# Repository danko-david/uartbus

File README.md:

# UARTBus and infrastructure

## Goal of the project
The project goal is to connect microcontrollers together on wire at minimal
cost (wiring, external peripheral components) and build a decentralized
sensor-actuator network where the node's can interact with each other and 
the microcontroller's software can be upgraded from the bus. This bus should be
connectable to a computer system (Desktop/Server PC, Raspberry PI, etc) to
achieve complex controlling by interacting with the sensors, actuators with
higher level softwares.

## Solution

The way to satisfy these requirement is to design and implement:
  
- new bus system for microcontrollers based on UART peripheral,
- lightweight RPC library for microcontrollers,
- bus gateway for computers,
- so called "host program" that implements common functionalities and manages
	application upload into the microcontroller. 
- a utility to connect softwares to the bus (through bus gateway)
- a higher level representation of bus devices (implemented in java)

## Feature list:

** Features related to bus: **

- microcontrollers connected together using built in UART peripheral and only
	one (pair when no ground) wire
- The bus forms a node based (device with address) network, but can be used
	to construct message based network like CAN.
- This is a multi master bus: any node can send message to any other node and
	vica-versa.
- Supports broadcast messages and that way device groups (negative device 
	addresses).
- Handles transmission collisions, retransmit and has a simple anti flood
	protection
- Interrupt based packet receive (send happens in blocking mode for now)
- Packet transmission based on transmission/idle time slots
- The core (ub) library is designed to be device agnostic and can even connect
	to multiple bus at same time when there's more UART peripheral available.
- The project contains a small footprint RPC library with function namespace
	capability used to order functions into namespaces like in OOP languages.
- variable length addressing

** Features related to the infrastructure: **

- The project contains a so called 'uart bootloader' (that's a wrong name, it
	should be host application or something else) that implements basic
	functionalities and code upload capability. Of course applications written
	directly for the microcontroller won't work, but i've created an
	`app_wrapper` used to compile applications can be uploaded to a node.
	TODO compiler, source, etc
- The project contains a bus gateway source written for ATMega2560, used to
	connect PC to an UARTBus.
- Java: At the PC side there's a server application (written in java) that makes
	the bus available through a JSON RPC server, this makes possible multiple PC
	application to connect the bus simultaneously even for different languages.
- Rust: the same CLI as one small executable without JVM, for embedded computers
	(Raspberry PI, routers), see [source/rust/uartbus](./source/rust/uartbus/README.md).
- Java: CLI application: `ping` to ping nodes, `console` to send command to
	devices, `packetloss` to measure packet loss ratio between bus gateway
	and node, `collisionPacketloss` to measure packet loss and duplication
	when send a broadcast packets that results race to access the bus.
	`upload` upload application code to a device with has uartbus bootloader on
	the board.

## Example usage

TODO: There's an easier way to try it out by yourself, using only arduino
and generic FETs (or BJTs with no opening delay in switching mode)

## Documentation

See: [Documentation index](./doc/index.md)   
All level and detail are implemented as small portion and bound so loosely
together to anyone can reuse the smaller piece of building blocks for custom
project.  

Eg: you can use OSI-{1,2} levels and skip the upper ones and
create a message based bus like as the CAN bus works. Or reverse: use CAN on the
lowest level and use the infrastructure.

## Short implementation explanation

### OSI-1: Physical layer

The bus data line consist of one wire pulled up to the bus Vcc voltage.
This line can be pulled down by any node used to transfer data.

The microcontroller's UART port is connected to the bus using bus driver: 

(During the development: Vcc = 12V; Rbus = 500Ω; Rtx = 0Ω; 
Rin & Ronline = 10 KΩ; 120m twisted pair for GND and Bus wire; 115,2 kbps)
(Note: this BS170 tolerates ±20V of Ugs voltage so can be connected directly to
the bus wire, but this might be risky when dealing with high transient voltage.
Solution: Connect TVS diode between `Bus` and `GND` wire. See documentation)

This is a simple level driver which makes the byte sent on the TX port appears
in the `Bus` line and data appears on the `Bus` wire translated to the RX port
with the proper logic level. This also means what we send on the TX we receive
on the RX. This used for transmission error and collision detection.

- Channel 1, Red: Bus wire signal 2 V/Div 
- Channel 2, Yellow: RX wire signal 1 V/Div

### OSI-2: Datalink layer

In this context, packet is interpreted as a sequence of byte in a time frame.
The time frame starts at the first sent byte and ends after the time of 2
(default value, but configurable) byte time transmission idle period.

A demonstration of UARTBus packages with collision handling (and retransmission)
using two nodes plus one bus gateway.
(This is an early development oscillogramm, timing not properly optimized)

- Channel 1, Red: Bus wire signal 2 V/Div 
- Channel 2, Yellow: RX wire signal of the first device 1 V/Div

1) Bus gateway sends a broadcast ping packet
2) Collision occurred, both node cancels the transmission and step back for a
	random time (longer wait time to the next transmission start)
	(Ethernets style collision handling)
3) First node "wins the arbitration" and sends the response pong packet
4) Second node also retransmit the pong packet that collided previously
5) No packet to send. Back to idle state.

### OSI-3: Network layer

Every node receives every packets on bus. This makes possible to create
broadcast addresses (0 is a general broadcast address) and device groups by
using negative addresses for this purpose.

Instead of using fixed int{8,16,32,64}_t for addressing, i've created a so
called variable length addressing:

- If we choose int8_t, every packet has only two byte of overhead at the
	addressing, but only 128 group 1 broadcast and 127 device address available.
- If we choose int32_t, every packet has 8 byte overhead, but addresses can go
	at group to 2_147_483_648, one broadcast and 2_147_483_647 device address.

To balance between this extreme cases i've created an encoder/decoder that
enables short address bytes when addresses are low (between -64 and +63) and 
increase address length when assign higher addresses.

|   | 7. bit | 6. bit | 5. bit | 4. bit | 3. bit | 2. bit | 1. bit | 0. bit |  
| --- |:---:|:---:|:---:|:---:|:---:|:---:|:---:|:---:|  
| First byte | E | S | A5 | A4 | A3 | A2 | A1 | A0 |  
| Nth byte | E | A6 | A5 | A4 | A3 | A2 | A1 | A0 |  

Byte scheme:

- E: Extend: Address continued on the next byte. The in last address byte this
	bit is 0. 
- S: Signum: sign of the whole number. Used only in the first byte. If set
	address is converted as: -(addr+1)
- An: address bit.

Example for one byte addresses:

| Address | First byte |  
|:---:|:---:|  
| 0   | 0000_0000 |  
| -1  | 0100_0000 |  
| 16  | 0001_0000 |  
| -16 | 0100_1111 |  
| -64 | 0111_1111 |  
| 63  | 0011_1111 |  

Example for two byte addresses:

| Address | First byte | Second byte |  
|:---:|:---:|:---:|
| 128   | 1000_0001 | 0000_0000 |  
| -128  | 1100_0000 | 0111_1111 |  
| 8191  | 1011_1111 | 0111_1111 |  
| -8192 | 1111_1111 | 0111_1111 |  

These types described as (s)vint_t (signed variable int) but it is not a real
type which the compiler knows, just a notation. (There's an implementation for
uvint_t if you use only unsigned values.)

The default packet scheme of the project:

- svint_t destination address
- svint_t source address
- uint8_t[n] payload
- uint8_t crc8 packet checksum

### OSI-{4,5}: Transport and Session layer
All packets are datagrams. There's no transmission control mechanism implemented
__yet__.

### OSI-6: Presentation layer

I've created a small footprint RPC library for microcontrollers. The
namespace path and function parameters just placement in the packet after each
other. The dispatcher function relays the request to the proper RPC path, and
the registered RPC call handler extracts the parameters executes the query and
responses the packet.

A request parsed into a `struct rpc_request` located in
[./source/uc/utils/lib/rpc/rpc.h](./source/uc/utils/lib/rpc/rpc.h).  

This request is dispatched through a RPC namespace chain. For example see:
[./source/uc/bootloader/ub_bootloader.c](./source/uc/bootloader/ub_bootloader.c)
how RPC_NS_FUNCTIONS constructed and where this chain used as a parameter.

When a namespace matched `procPtr` incremented, so in next processing stage
the it will be continued from the next byte (pointed in the payload by
the procPtr which is incremented right now)

The pointed function may dispatch again, or it can be a function which processes
the request. The `reply` function pointer in the `struct rpc_request` used
assemble and send response packet.

Example: in the bootloader (aka: uart host application) there's some pre-defined
RPC namespace and functions which provides unified functionality for all devices
on the bus.

- 0: the 0.th namespace is reserved for response packets.
- 1: Bus functions
	- 0 ping: responses and empty message as a pong packet
	- 1 replay: responses the request payload
	- 2 user_led: controls the PORTB5 LED (arduino 13 port led) 0 = off, 1 = on,
		2 = toggle: always replays the current (after the request) state of the
		led
- 2: Bootloader functions:
	- 0 power functions:
		- 0 hardware reset (using wdt timeout)
		- 1 software reset (jmp 0x0)
	...
	- 4: flash functions:
		- getFlashStage: is the device under code upload?
		- getAppStartAddress: returns the application start address
		....
		
And so on, for full namespace specification see documentation.

To turn on the user led you have to send a packet with payload of:    
1:2:1 => (1) Bus functions => (2) user led handler function => (1) parameter    
this returns with the response:    
0:1:2:1 => (0) response packet => (1:2) namespace and function path => (1)
	response parameter aka the led is turned on.   

To invoke a hardware reset:
2:0:0 => (2) Bootloader functions => (0) power functions => (0) hardware reset   
No response generated, because committed a hardware reset immediately.

This namespace tree is extendible to any depth, and designed to the application
developer can attach new function into this tree.

At the other side, on the PC in java, this RPC namespace tree is modeled with
objects, see: `UartBusDevice.getRpcRoot()` . But the best thing: i've created
a mechanism to describe interfaces for this RPC namespaces and functions with
the known types, and java (using proxies) generates namespace object and
function you can call right from java. For example see: UbBootloaderFunctions
and for a real application that uses this see: UartbusCodeUploader

### OSI-7: Application level

In the directory .source/uc/bootloader/ you find the source of the bootloader
(the naming is wrong, it's more likely be called as uart host application)
This implements the basic unified functionality described earlier and also makes
possible to manage application code upload.

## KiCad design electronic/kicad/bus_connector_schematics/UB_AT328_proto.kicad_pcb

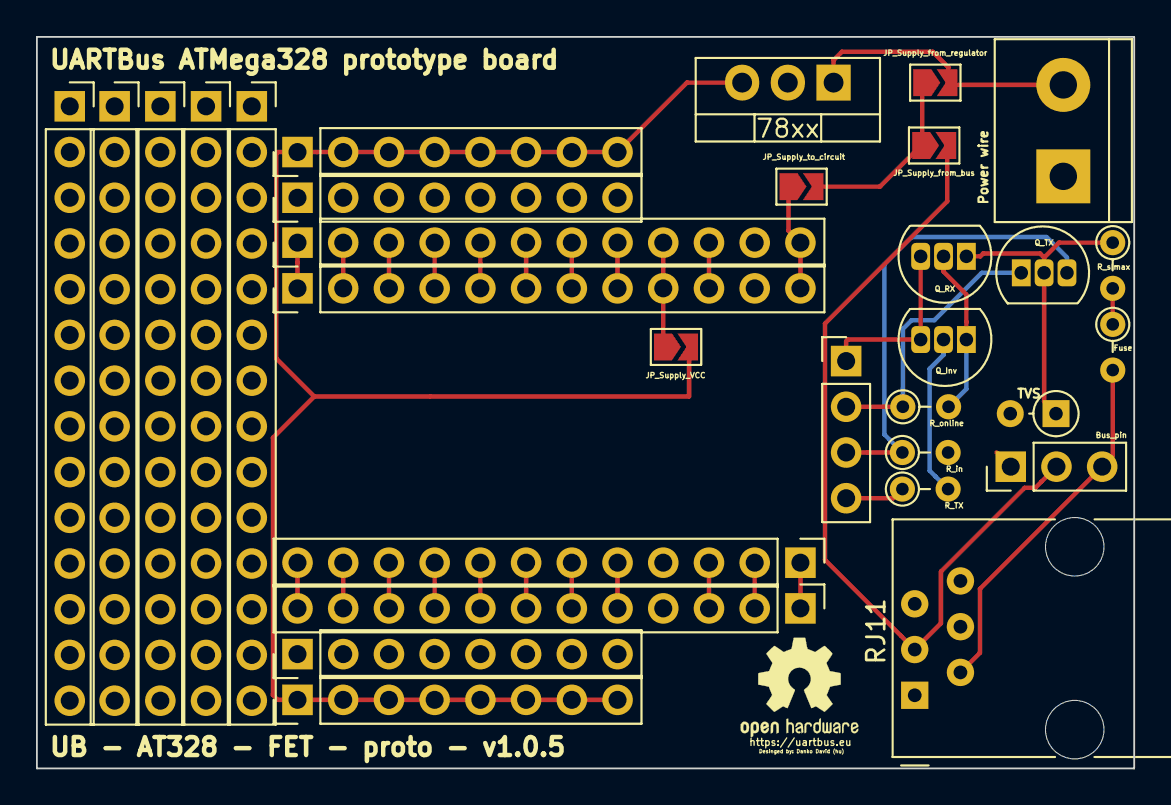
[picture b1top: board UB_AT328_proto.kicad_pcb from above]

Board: 2 copper layers, 61.0 x 40.6 mm, 17 parts (0 on the bottom side), 12 nets.

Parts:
78xx: 7805; TO-220-3_Vertical
Bus_pin: CONN_01X03; PinHeader_1x03_P2.54mm_Vertical
Fuse: Polyfuse; R_Axial_DIN0204_L3.6mm_D1.6mm_P2.54mm_Vertical
JP_Supply_VCC: Jumper_NO_Small; SolderJumper-2_P1.3mm_Open_TrianglePad1.0x1.5mm
JP_Supply_from_bus: Jumper_NO_Small; SolderJumper-2_P1.3mm_Open_TrianglePad1.0x1.5mm
JP_Supply_from_regulator: Jumper_NO_Small; SolderJumper-2_P1.3mm_Open_TrianglePad1.0x1.5mm
JP_Supply_to_circuit: Jumper_NO_Small; SolderJumper-2_P1.3mm_Open_TrianglePad1.0x1.5mm
Power wire: Screw_Terminal_1x02; TerminalBlock_bornier-2_P5.08mm
Q_Inv: BS170; TO-92L_Inline
Q_RX: BS170; TO-92L_Inline
Q_TX: BS170; TO-92L_Inline
RJ11: RJ12; RJ12_Amphenol_54601
R_TX: R; R_Axial_DIN0204_L3.6mm_D1.6mm_P2.54mm_Vertical
R_in: R; R_Axial_DIN0204_L3.6mm_D1.6mm_P2.54mm_Vertical
R_online: R; R_Axial_DIN0204_L3.6mm_D1.6mm_P2.54mm_Vertical
R_sImax: R; R_Axial_DIN0204_L3.6mm_D1.6mm_P2.54mm_Vertical
TVS: D_TVS; D_DO-34_SOD68_P2.54mm_Vertical_AnodeUp

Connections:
/bus_connector_2_FET/Bus_Data: Bus_pin.3, Fuse.2, RJ11.2
/bus_connector_2_FET/Bus_Gnd: 78xx.2, Bus_pin.1, Power wire.1, Q_Inv.3, Q_RX.3, RJ11.5, R_in.2, TVS.2
/bus_connector_2_FET/Online: Q_TX.1, R_online.1
/bus_connector_2_FET/RX: Q_TX.3, R_in.1
unnamed: Bus_pin.2, JP_Supply_from_bus.2, RJ11.3
unnamed: 78xx.1, JP_Supply_from_regulator.2, Power wire.2
unnamed: Q_RX.1, Q_TX.2, R_sImax.1, TVS.1
unnamed: Fuse.1, R_sImax.2
unnamed: 78xx.3, JP_Supply_VCC.2
unnamed: JP_Supply_from_bus.1, JP_Supply_from_regulator.1, JP_Supply_to_circuit.2
unnamed: Q_Inv.2, R_TX.2
unnamed: Q_Inv.1, Q_RX.2, R_online.2

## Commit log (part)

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2019-02-17 Initial Rpc server and client implementation POM: build UartBus RPC server as a startable jar
2019-02-18 typo fix - use newest version of RPC that supports variadic argument RPC calls - Cli class that dispatches the cli parameters between modules - building Cli dispatcher class as mainfest main for the 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
2019-02-18 fix pom tag misplacement
2019-02-18 another mispacement fix
2019-02-18 Working console (tested by hand)
2019-02-19 add the WorkingDirectory
2019-02-19 - some useful scripts - tie compiler into the cli dispatcher - ++version
2019-02-25 - Some TODOs in the doc directory - replace bus_connector to the adruino verions - app wrapper code
2019-03-02 + address pack/unpack +tests + code uploader skel + improved packet assembler + common cli parameters outsourced into UartbusCliTools class + UartbusModel
2019-03-02 - ignore debug output files (*.asm and *.sizes) - endianness detection code - compile_and_upload.sh - fix to compile ub_bootloader.cpp
2019-03-03 + makefile and uploader script for uartbus_connector (+gitignore .e files) + posix_errno.h moved to common place + new cli utilities: - ping - intel hex file validation and real code size (well, linu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
2019-03-03 - outsource rpc utility functions - use less parameters by packing them into `struct rpc_request` - implement and use variable length addressing
2019-03-09 now with selectable baud rate
2019-03-09 - test bus upgraded to 115200 baud - refactor to junk out options like ub_cfg_external_read, ub_cfg_read_after_send, ub_cfg_interrupt_bad_send use interrupt (using the option) or blocking (neglecting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
    - collision detection and handling (work in progress)
2019-03-12 updated DOC (TODO and completition list) - Java: UartBus model class with UartBusDevice and tools. utilities: - Packet reader - Uartbus device Rpc tree with LazyImplementation: - built in Namespace a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
    ubb: enable multiple request "in fly"
    TODO packet output queue
2019-03-17 add Cli Tools: Packetloss and CollisionPacketloss
2019-03-17 calc fix
2019-03-25 proper state stepping and timeout check separation
2019-03-29 move send fairwait back, because if we keep in sending state, we won't gonna receive the packet.
2019-03-29 modify sending state, enter fairwait immediatly, because if we keep in sending mode we might miss the start of a package to receive
2019-03-30 - preparing code uploader implementation: - intel hex file code extractor - cli: uploader checks
    - Ub RPC: annotation for safe retransmittable RPC calls and implementaion
    of automatic tetransmission, error handling
2019-03-31 proper RPC result extraction using the declaration (java.lang.reflect.)Type app wrapper + compiler simple test app Code uploader (ihex file upload with cli)
2019-04-07 - code uploader fixes and use smaller size for verifivtion (due a packet size bug) - plus bus function: replay - bootloader/host: - flash write condifiton fix - RPC: accept one byte code package - op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
    - modify registrateable user application packet hook function signature
    - ub app:
    - compiler script
    - temporary modification for uploaded code, until BSS location get fix
2019-04-19 - remove platform depend code from ub.cpp - successfull experiment for eliminating bss segment
2019-04-20 A better bus connector
2019-04-20 fix last packet value flush wait on interrupt receive
2019-04-21 separate send and fairwait, cover yet another point of potential packet loss
2019-04-22 How to break runtime without get any notice, fix and explanation
2019-04-22 - new BASIC RPC functions (NS:1, control "user_led" aka arduino PIN 13 LED, get current time to debug timing related issues, and rand issues) - bootloader: - predict incoming transmission using PCINT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
    However something went so terribly wrong, at this point i can't figue out what caused that.
    So now - because now time measure is accessed trought function pointers - i take out the old
    good novaprova and write some test to document exact behavior and proof with it.
2019-05-19 - rewrite: currentUsec => current_usec - add struct uartbus* ("this") pointer to current_usec and rand (used for testing) - form a test file and build script
2019-05-20 - add tests - fineing ub_manage_connection result value - fix timing issues discovered with the tests - add missing event emitting, discovered with tests.
2019-05-20 - dependency downloader script - record events in tests - add send event test
2019-05-20 + tests: receive and retransmit
2019-05-28 - fixing tests - CLI: loggin bad packet escape sequence - pending: something is wrong with the bus connector, it miss some bytes when writing to PC_SERIAL wire. This happens in the interruption metho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
2019-05-29 fix: - ub_app source order - cli code uploader: restart event subscription - cleanup PORTB ^= 0xff - provide micros function for ub_app - send_packet add destination NS parameter
2019-06-15 README.md
2019-06-25 doc fixes move cli application to the matching package
2019-06-28 documentation
2019-06-28 doc fix
2019-06-28 For response packet, use the 0 namespace
2019-06-29 Arduino/wiring compatible compilation for atmega328
2019-06-29 - tune code upload timeouts and add skip verification cli option - fix typos
2019-08-02 change terminology `bus connector` => `bus gateway` documentation index: documentation TODOs
2019-08-17 - fix calculation of microsecounds when using clock frequency that's not multiple of of whole 1 MHz - kick out some unused gloval variable in the ub_atmega.c - add clock frequency as a parameter to c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
    Well something not work when using atmega with 1.8432 MHz crystal... further investigation needed
2019-08-17 Feature to construct reflectable tree of RPC nodes and functions. And external software can access and get known about the RPC tree and the functions in there, the signature and retval of the functio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
    This gonna be a resource demanding solution, that's why wasn't part of the basic
    functionality and codebase
    Im still in progress to get inspiration for the desing of this by working on an
    implementation Java SNMP server, zabbix and autodiscovery, information providing mechanism.
2019-08-17 Create LICENSE
2019-09-15 Bus gateway for atmega328 using software serial
2019-09-15 add more test, but these doesn't spot the bug i saw. so added debug and trace logging
2019-09-25 - doc: documenting discovered bus connector handycap - rpc server: reconnect socket on error - loopback sent packages
2019-09-25 - use the newest jvx-core - add blink CLI feature - add sql_log feature - extract LOOPBACK CLI option to UartBusCliTools - add reconnect: add missing sleep call
2019-09-25 increment version used to start publishing package
2019-10-02 - arduino compiler scripts (two script: all and selectable libraryies) - add "-Wl,--gc-sections" to optimise out unused code when compiling arduino Code uploader: - logging instead of using System.ou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
2019-10-06 - scripts: determine the proper working directory even if it is soft linked - complilation scripts: arduino selective libarries, use the linux default path - typo fix - host flasher: - fault protecti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
2019-10-15 add more explanation document
2019-10-15 - uartbus host test code added - test cases added that spotted a bug and ensures other way than to reproduce the bug that the code upload process is works - fix the bug (also tested on a real device)
2019-10-26 fix packetloss statistic calculation condition
2019-10-27 - pull out retry logic to a reusable form - Improve serial reconnection management - easy to use reconnection to the TCP connections
2019-10-27 fix typo
2019-11-05 rename bus_connector to bus_gateway (term harmonization)
2019-11-05 Rework bus gateway: - outsource gateway common parts - fix 2560 compilation
2019-11-09 - ub rpcServer: improved reconnection linux_uartbus_gateway: add some serial options that doesn't helped with USB serial (pl2303) but might help on raspberry with native (PL2303)
2019-11-10 - redirect communication process's stderr to Java stderr - improve communication process error reporting - gitignor built communication process
2019-11-10 - rpcServer: print communication process exit status - linux_bus_gateway: replace abort()s to exit(n) - uartbus host compiler: add baud rate as parameter
2019-11-10 add two more important assertation
2019-11-10 linux_uartbus_gateway: debugging inforamtion printage depend now on ENV
2019-11-10 yet another point of failure to sense of deadline miss, spotted, evoked, fixed, tested
2019-11-12 add another important assertations
2019-11-12 - add root CI hooks to get dependencies - add fully automated script that CI server can call directly
2019-11-13 - yet another fix to machine agnostic build - add indirect dependencies
2019-11-13 fix another compilation probleam on bare machine
2019-11-18 echo when all hook executed successfully. It's help me to verify the jenkins (or any other) build completed or not, so where is the problem in the build or in the result collection process?
2019-11-20 Modify arduino library. It compiles without warning, it's time to test.
2019-11-20 aruino library: it not only compiles, it's works too.
2019-11-22 pull out the uartbus specific part from the bootloader, this makes possible to inject other bus handler
2019-11-22 tie ubh_linux to the automated build fix a build error
2019-11-26 - linux ubh compiler script - read ubh address from ENV - make ubh_impl_call_app overwriteable by making weak. this can used to compile cusomt apps
2019-11-26 remove unused source
2019-12-02 DRY: use stuffs from libraries instead
2019-12-16 add reflect namespace
2019-12-18 RPC reflection capability in progress
2019-12-20 - pass trought extra CLI options - rewrite urls from .md files to .html on rendering
2019-12-29 - site todos md - replace footer to full sentence
2020-01-04 Working RPC namespace walking features: - new types uint{8,16}_t, integrated into the UB rpc layer - existing NoReturn, V{,U}Signed types integrated into the UB rpc layer - c: RPN feature
    TODO publish the sandbox code that used to develop this function.
2020-01-04 better looking timestamp
2020-01-04 mixed up
2020-03-14 Add dockerfile to build the project in a container
2020-04-12 fix: exit ub rpcServer when no reconnection required
2020-04-13 - Cli: version utility - RxTx serail alternative: failed by hand test
2020-04-26 code uploader: implement proper reconnect
2020-05-30 Ub: - cli: grab & reboot command App compile srcipts, enable to inject of alternative arduino source library
2020-06-24 bootloader: add `manage_bus` function app_wrapper: working static constructor initialisations
2020-06-25 Release rpc parallal request feature with slightly modifications
2020-06-25 make ub console flexible and more reusable
2020-06-25 add raw packet end "feature" to UartBus
2020-07-12 log PCB design mistakes (for future fix)
2020-07-21 Achieveing a milestone: Direct mode now available. Direct mode: You can upload the bootloader without uartbus. In this case the bus is replaced with the gateway code, so on the PC side, you can conne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
2020-08-23 proper __do_clear_bss and __do_copy_data implementations
2020-08-23 Arduino source compilation: add debugging option ub_ardulib_upload: add shorthand script to compile and upload in one call
2020-08-25 Working on Uartbus Services - i need a cherry pick, os committing work in progress files
2020-09-14 1.7.0 Release day!
    New features:
    - VirtualUartBus: create internal uartbus server (without RPC bound). This
    is a connection source you can use to start multiple UartBus instances.
    - UartbusServiceBridge: achieves the feature to connect java based uartbus
    network service to the bus and make these services available to other
    nodes on the bus. It's simple as creating a new POJO object with
2020-09-16 test fix
2020-10-07 improve documentation and documentation generation
2020-10-07 contribution documentation
2020-10-07 build fix
2020-10-13 Bump junit from 4.11 to 4.13.1 in /source/java/uartbus
    Bumps [junit](https://github.com/junit-team/junit4) from 4.11 to 4.13.1.
    - [Release notes](https://github.com/junit-team/junit4/releases)
    - [Changelog](https://github.com/junit-team/junit4/blob/main/doc/ReleaseNotes4.11.md)
    - [Commits](https://github.com/junit-team/junit4/compare/r4.11...r4.13.1)
2023-05-23 Bump sqlite-jdbc from 3.25.2 to 3.41.2.2 in /source/java/uartbus
    Bumps [sqlite-jdbc](https://github.com/xerial/sqlite-jdbc) from 3.25.2 to 3.41.2.2.
    - [Release notes](https://github.com/xerial/sqlite-jdbc/releases)
    - [Changelog](https://github.com/xerial/sqlite-jdbc/blob/master/CHANGELOG)
    - [Commits](https://github.com/xerial/sqlite-jdbc/compare/3.25.2...3.41.2.2)
    ---
    updated-dependencies:
2026-05-22 fix on new GCC optimisations
